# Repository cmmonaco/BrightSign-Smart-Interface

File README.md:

# BrightSign Smart Interface

The BrightSign Smart Interface (BSSI) is a system developed expand the capabilities of the [BrightSign](https://www.brightsign.biz/) digital signage controllers. A BrightSign has 8 GPIO pins used to control playback or out elements, however, the IO is limited to simple switching input making it less useful for interactive installations where complex input is used. The BSSI system is a set of boards that contain an Arduino along with support hardware specific to the interface type. This allows for the use of multiple and complex inputs and additional processing while controlling playback on the BrightSign. Current BrightSign players no longer support the connection type used in the BSSI.

## BSSI System

The BSSI system presently consists of three boards: the main board and two expansion boards: the GPIO board, and the industrial sensor board.

### Main Board

The main board contains the Arduino and serves as the primary interface to the BrightSign. The main board also contains a power adapter, allowing the Arduino and other peripherals to be powered externally rather than by the BrightSign.

### GPIO Board

The GPIO board simply break outs the remaining Arduino IO to headers. The board has locations on each pin for pull-up resistors and pins 10 and 11 are buffered (this can be bypassed).

### Industrial Sensor Board

The industrial sensor board can accept up to 7 channels of NPN type industrial sensors, 8 digital GPIO, and two analog inputs. It uses a port expander IC to achieve the high number of GPIO in addition to the sensor channels. The NPN sensor are connected using the following hardware interface:

## BSSI Library

An Arduino library for use the the BrightSign Smart Interface is also available. See README located in library directory for details.

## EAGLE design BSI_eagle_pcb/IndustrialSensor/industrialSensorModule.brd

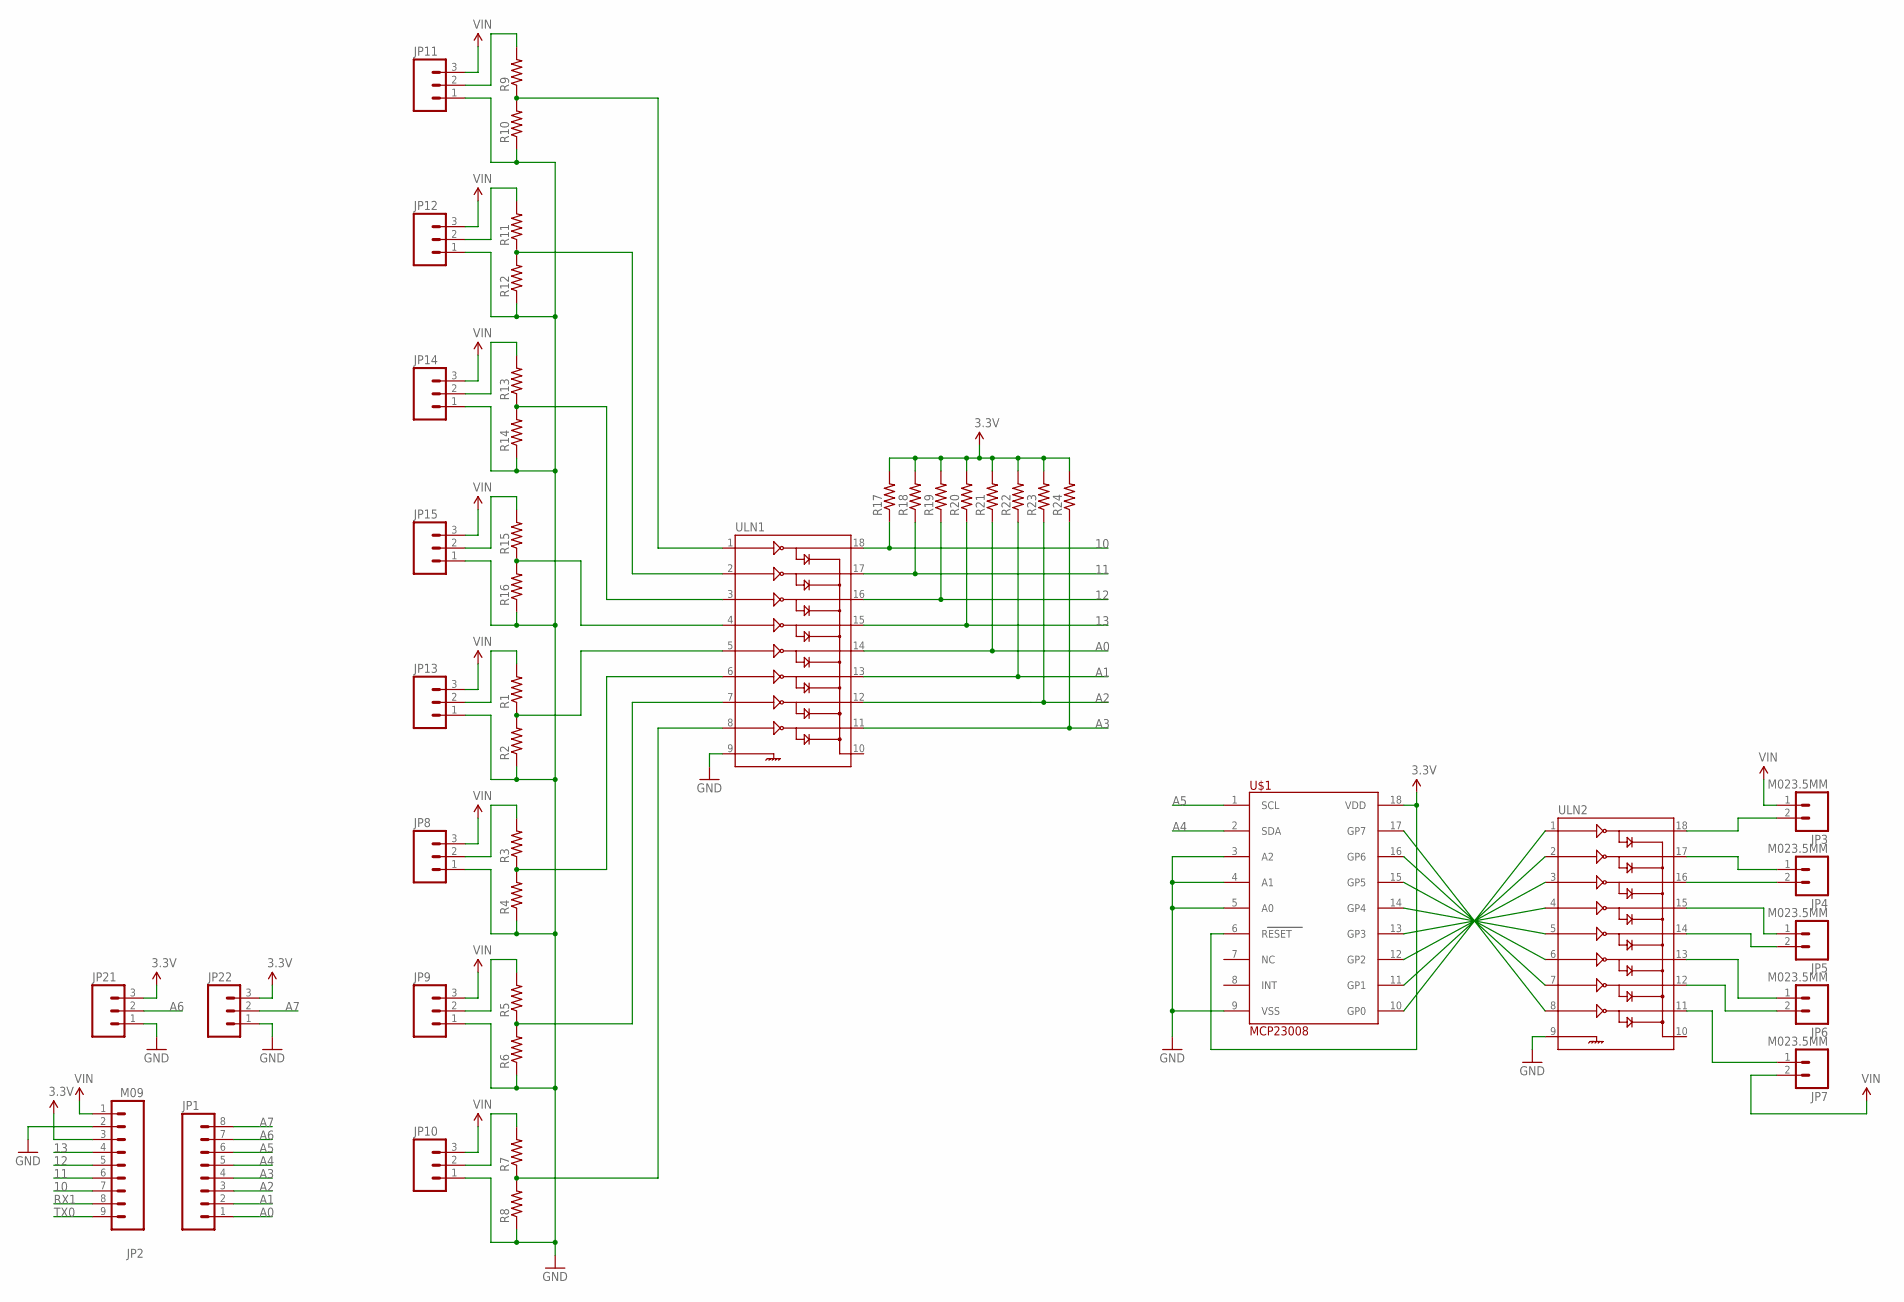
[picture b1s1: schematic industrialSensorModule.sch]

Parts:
JP1: M081X08; 1X08
JP2: M09; 1X09
JP3, JP4, JP5, JP6, JP7: M023.5MM; SCREWTERMINAL-3.5MM-2
JP8, JP9, JP10, JP11, JP12, JP13, JP14, JP15, JP21, JP22: M03SCREW; SCREWTERMINAL-3.5MM-3
R1, R2, R3, R4, R5, R6, R7, R8, R9, R10, R11, R12, R13, R14, R15, R16, R17, R18, R19, R20, R21, R22, R23, R24: RESISTOR1206; 1206
U$1: MCP23008; SOICW-18
ULN1, ULN2: ULN2803SOICW; SO18L

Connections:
3.3V: JP2.3, JP21.3, JP22.3, R17.2, R18.2, R19.2, R20.2, R21.2, R22.2, R23.2, R24.2, U$1.6 (RESET), U$1.18 (VDD)
10: JP2.7, R17.1, ULN1.18
11: JP2.6, R18.1, ULN1.17
12: JP2.5, R19.1, ULN1.16
13: JP2.4, R20.1, ULN1.15
A0: JP1.1, R21.1, ULN1.14
A1: JP1.2, R22.1, ULN1.13
A2: JP1.3, R23.1, ULN1.12
A3: JP1.4, R24.1, ULN1.11
A4: JP1.5, U$1.2 (SDA)
A5: JP1.6, U$1.1 (SCL)
A6: JP1.7, JP21.2
A7: JP1.8, JP22.2
GND: JP2.2, JP8.1, JP9.1, JP10.1, JP11.1, JP12.1, JP13.1, JP14.1, JP15.1, JP21.1, JP22.1, R2.1, R4.1, R6.1, R8.1, R10.1, R12.1, R14.1, R16.1, U$1.3 (A2), U$1.4 (A1), U$1.5 (A0), U$1.9 (VSS), ULN1.9, ULN2.9
unnamed: R1.1, R2.2, ULN1.5
unnamed: JP13.2, R1.2
unnamed: R3.1, R4.2, ULN1.6
unnamed: JP8.2, R3.2
unnamed: R5.1, R6.2, ULN1.7
unnamed: JP9.2, R5.2
unnamed: R7.1, R8.2, ULN1.8
unnamed: JP10.2, R7.2
unnamed: R9.1, R10.2, ULN1.1
unnamed: JP11.2, R9.2
unnamed: R11.1, R12.2, ULN1.2
unnamed: JP12.2, R11.2
unnamed: R13.1, R14.2, ULN1.3
unnamed: JP14.2, R13.2
unnamed: R15.1, R16.2, ULN1.4
unnamed: JP15.2, R15.2
unnamed: U$1.10 (GP0), ULN2.1
unnamed: U$1.11 (GP1), ULN2.2
unnamed: U$1.12 (GP2), ULN2.3
unnamed: U$1.13 (GP3), ULN2.4
unnamed: U$1.14 (GP4), ULN2.5
unnamed: U$1.15 (GP5), ULN2.6
unnamed: U$1.16 (GP6), ULN2.7
unnamed: U$1.17 (GP7), ULN2.8
unnamed: JP3.2, ULN2.18
unnamed: JP4.1, ULN2.17
unnamed: JP4.2, ULN2.16
unnamed: JP5.1, ULN2.15
unnamed: JP5.2, ULN2.14
unnamed: JP6.1, ULN2.13
unnamed: JP6.2, ULN2.12
unnamed: JP7.1, ULN2.11
RX1: JP2.8
TX0: JP2.9
VIN: JP2.1, JP3.1, JP7.2, JP8.3, JP9.3, JP10.3, JP11.3, JP12.3, JP13.3, JP14.3, JP15.3

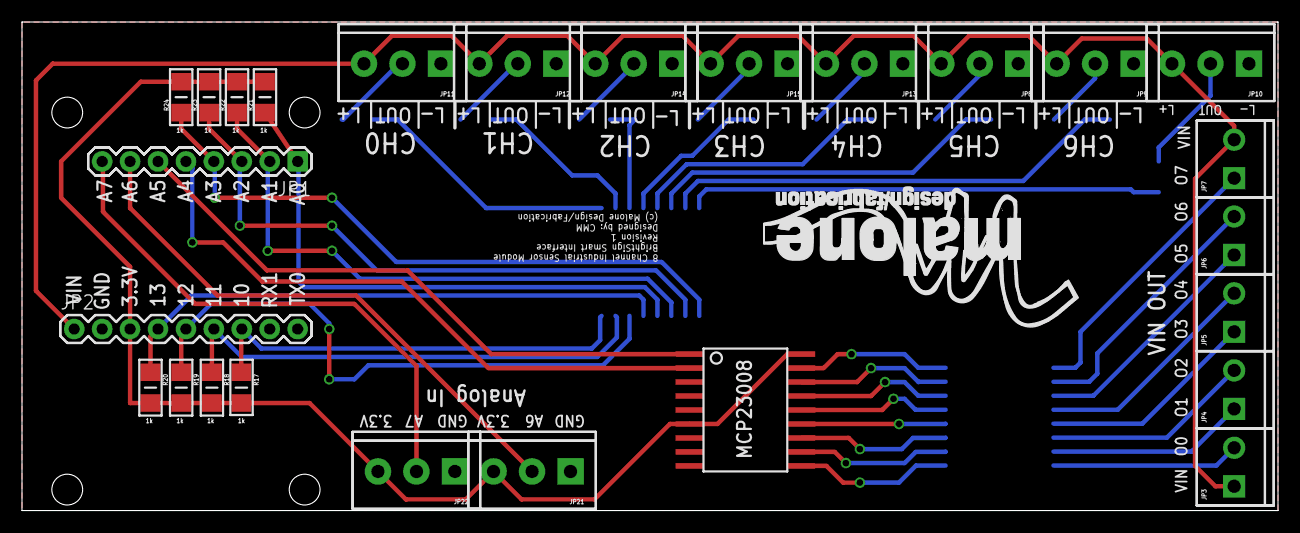
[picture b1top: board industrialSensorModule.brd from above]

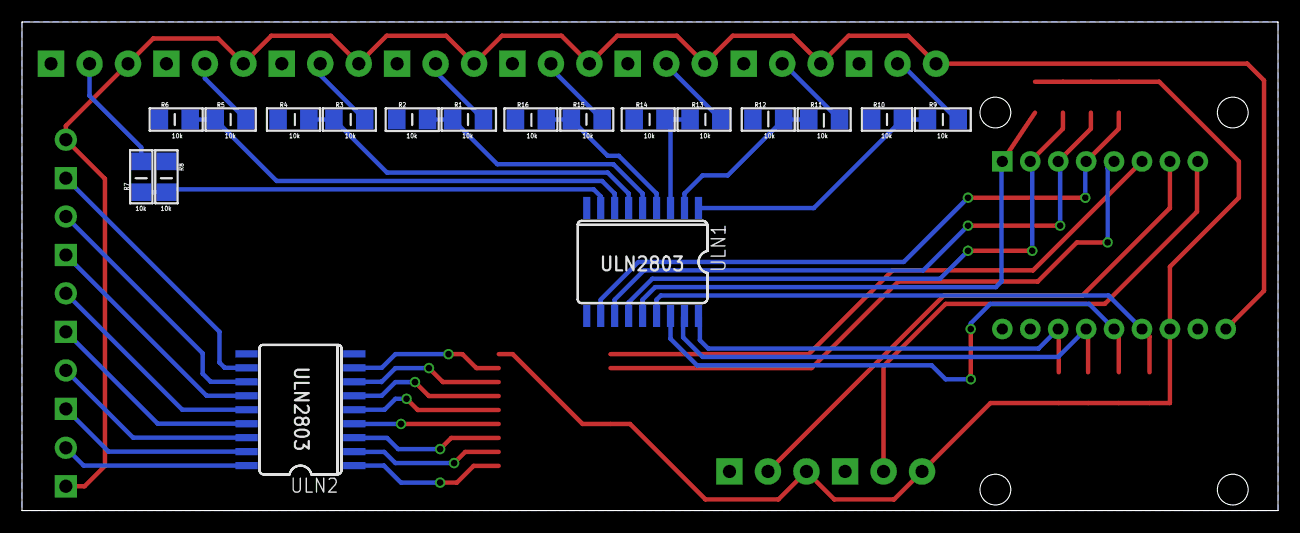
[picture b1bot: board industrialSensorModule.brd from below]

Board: 2 copper layers, 114.2 x 44.4 mm, 45 parts (18 on the bottom side), 47 nets.

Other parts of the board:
U$2: MALONE_LOGO

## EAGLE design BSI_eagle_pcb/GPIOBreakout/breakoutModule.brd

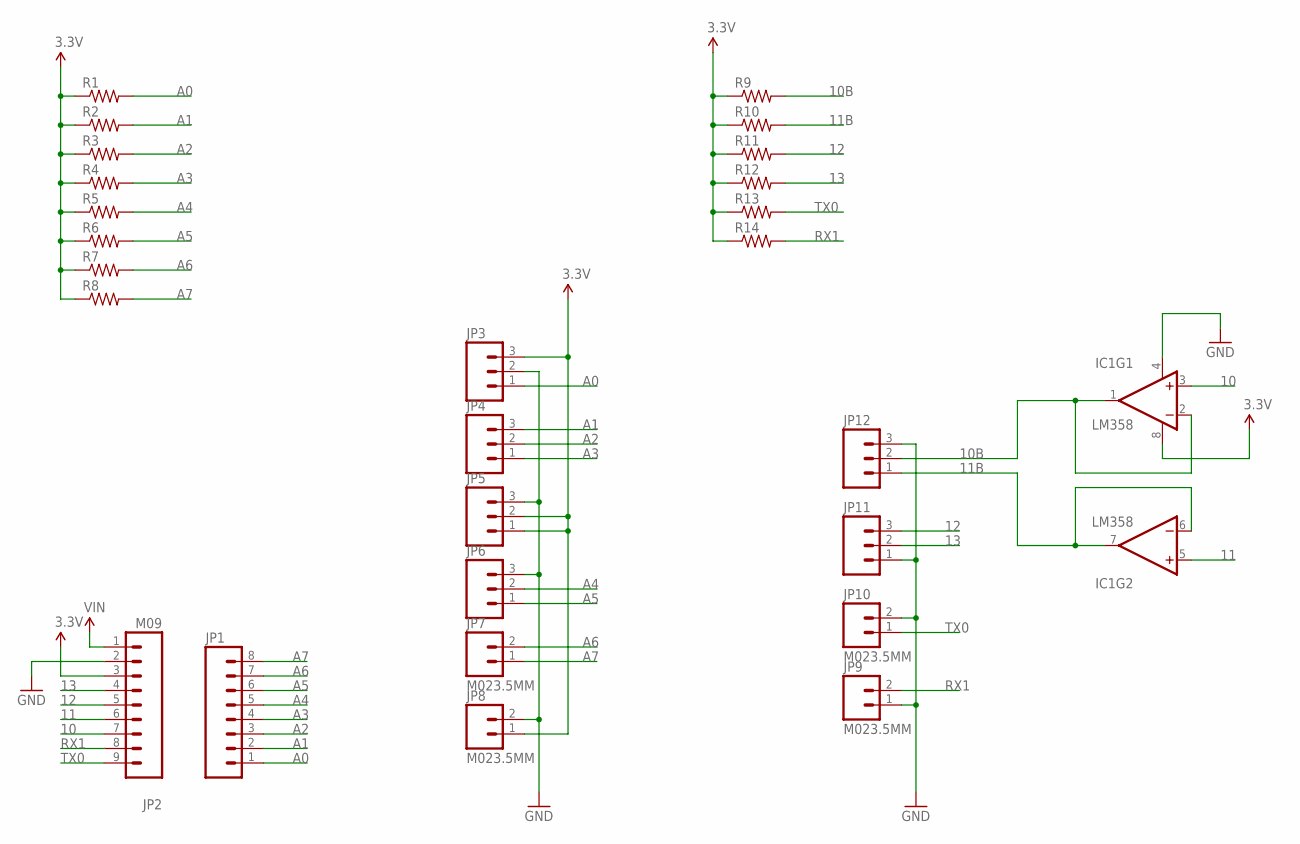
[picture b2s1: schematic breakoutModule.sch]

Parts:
IC1: LM358; DIP08
JP1: M081X08; 1X08
JP2: M09; 1X09
JP3, JP4, JP5, JP6, JP11, JP12: M03SCREW; SCREWTERMINAL-3.5MM-3
JP7, JP8, JP9, JP10: M023.5MM; SCREWTERMINAL-3.5MM-2
R1, R2, R3, R4, R5, R6, R7, R8, R9, R10, R11, R12, R13, R14: RESISTOR1206; 1206

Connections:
3.3V: IC1.8 (V+), JP2.3, JP3.3, JP5.1, JP5.2, JP8.1, R1.1, R2.1, R3.1, R4.1, R5.1, R6.1, R7.1, R8.1, R9.1, R10.1, R11.1, R12.1, R13.1, R14.1
10: IC1.3 (+IN), JP2.7
10B: IC1.1 (OUT), IC1.2 (-IN), JP12.2, R9.2
11: IC1.5 (+IN), JP2.6
11B: IC1.6 (-IN), IC1.7 (OUT), JP12.1, R10.2
12: JP2.5, JP11.3, R11.2
13: JP2.4, JP11.2, R12.2
A0: JP1.1, JP3.1, R1.2
A1: JP1.2, JP4.3, R2.2
A2: JP1.3, JP4.2, R3.2
A3: JP1.4, JP4.1, R4.2
A4: JP1.5, JP6.2, R5.2
A5: JP1.6, JP6.1, R6.2
A6: JP1.7, JP7.2, R7.2
A7: JP1.8, JP7.1, R8.2
GND: IC1.4 (V-), JP2.2, JP3.2, JP5.3, JP6.3, JP8.2, JP9.1, JP10.2, JP11.1, JP12.3
RX1: JP2.8, JP9.2, R14.2
TX0: JP2.9, JP10.1, R13.2
VIN: JP2.1

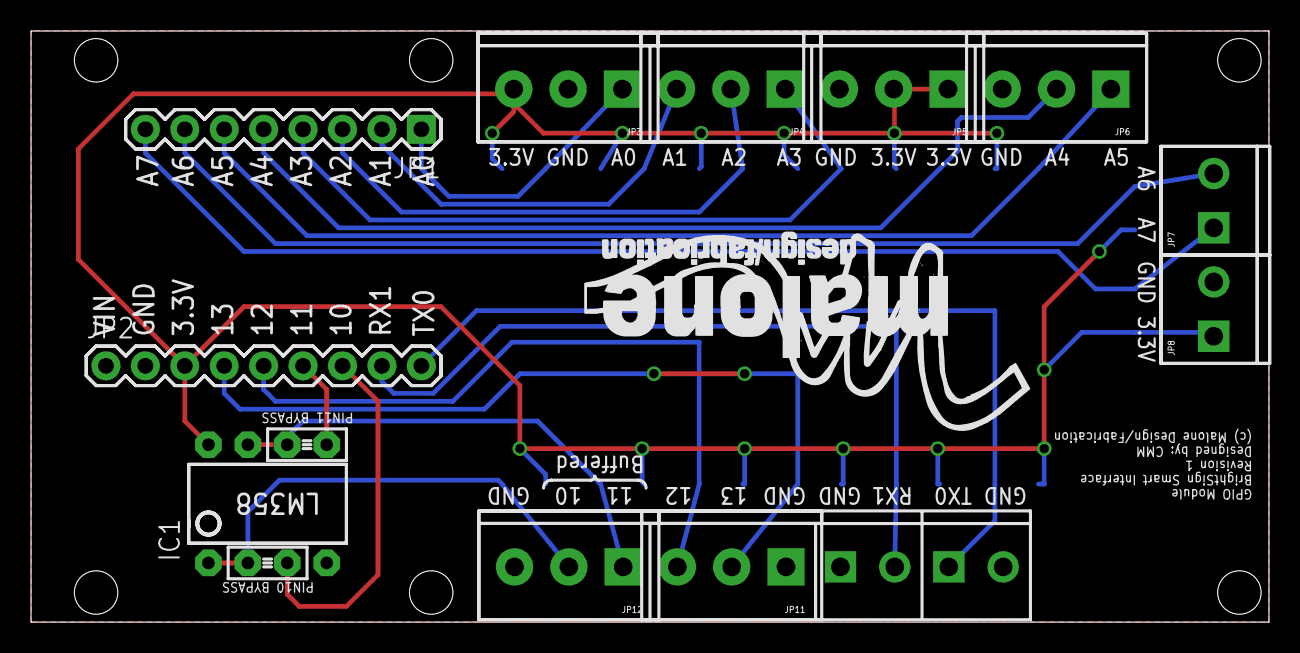
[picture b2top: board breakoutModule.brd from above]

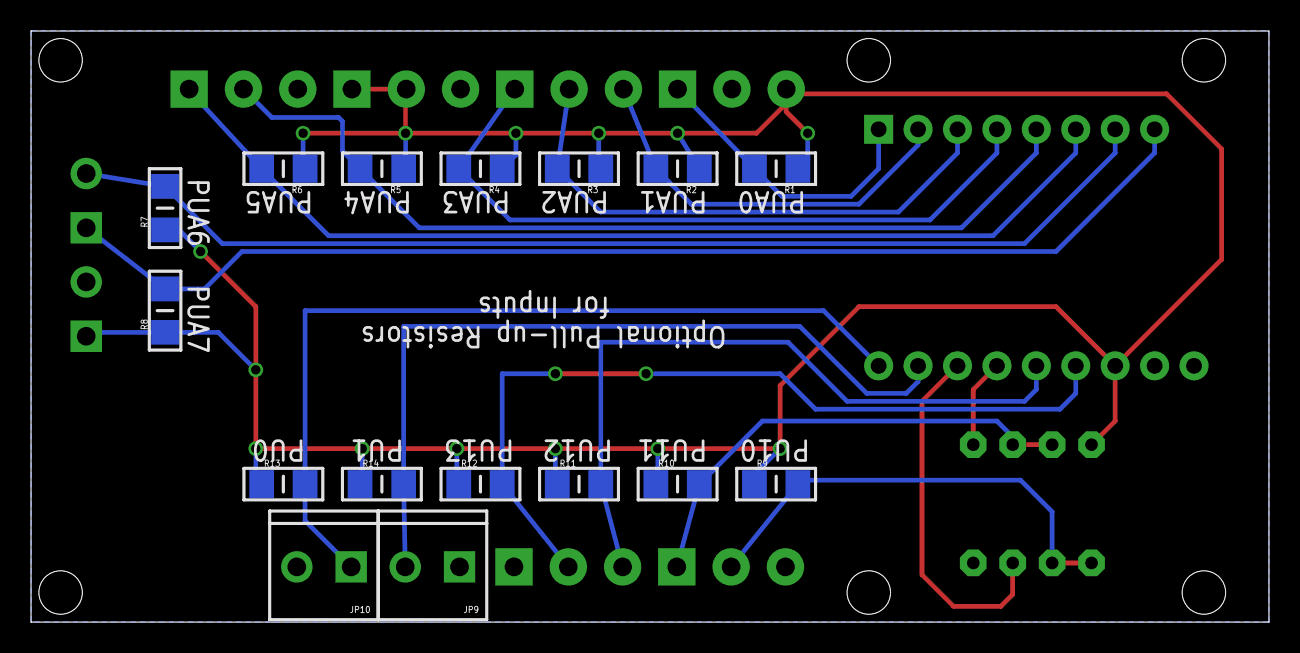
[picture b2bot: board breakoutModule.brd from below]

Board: 2 copper layers, 79.8 x 38.1 mm, 28 parts (16 on the bottom side), 18 nets.

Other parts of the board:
U$1: MALONE_LOGO

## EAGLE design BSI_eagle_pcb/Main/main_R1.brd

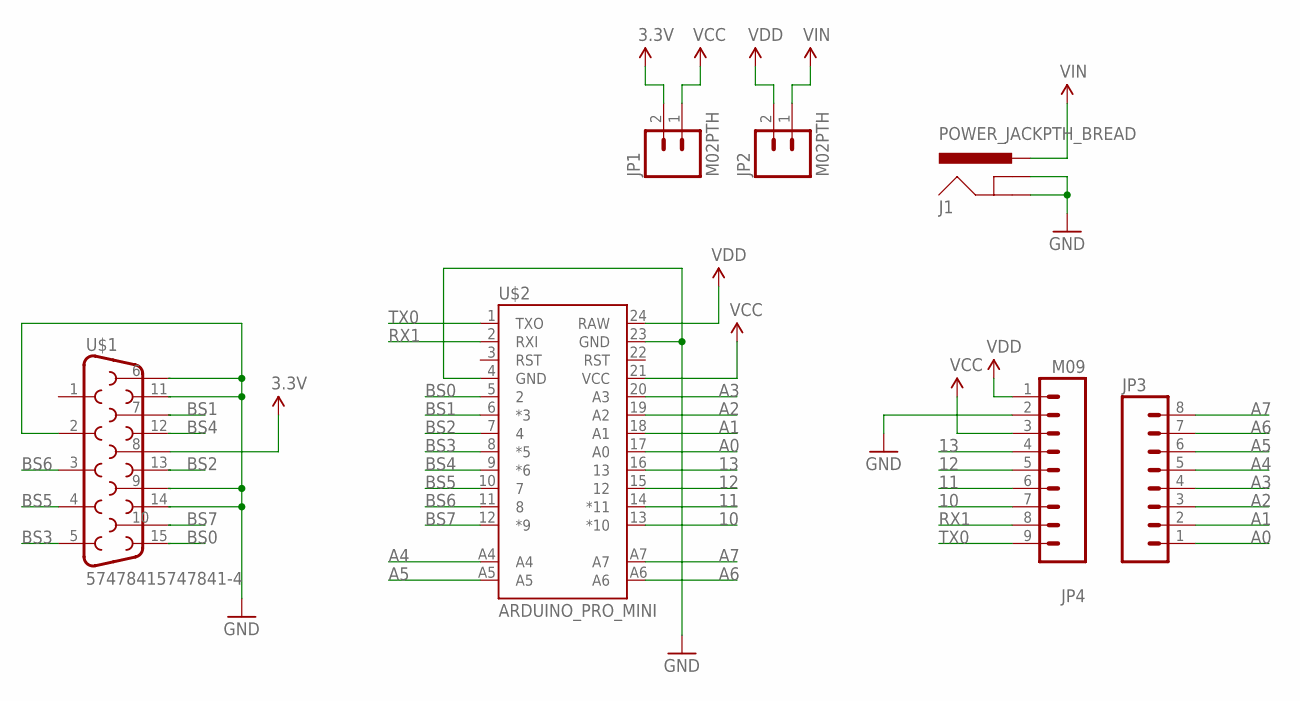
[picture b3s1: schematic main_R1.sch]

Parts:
J1: POWER_JACKPTH_BREAD; POWER_JACK_PTH_BREAD
JP1, JP2: M02PTH; 1X02
JP3: M081X08; 1X08
JP4: M09; 1X09
U$1: 57478415747841-4; 5747841
U$2: ARDUINO_PRO_MINI

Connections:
3.3V: JP1.2, U$1.8
10: JP4.7, U$2.13 (*10)
11: JP4.6, U$2.14 (*11)
12: JP4.5, U$2.15 (12)
13: JP4.4, U$2.16 (13)
A0: JP3.1, U$2.17 (A0)
A1: JP3.2, U$2.18 (A1)
A2: JP3.3, U$2.19 (A2)
A3: JP3.4, U$2.20 (A3)
A4: JP3.5, U$2.A4
A5: JP3.6, U$2.A5
A6: JP3.7, U$2.A6
A7: JP3.8, U$2.A7
BS0: U$1.15, U$2.5 (2)
BS1: U$1.7, U$2.6 (*3)
BS2: U$1.13, U$2.7 (4)
BS3: U$1.5, U$2.8 (*5)
BS4: U$1.12, U$2.9 (*6)
BS5: U$1.4, U$2.10 (7)
BS6: U$1.3, U$2.11 (8)
BS7: U$1.10, U$2.12 (*9)
GND: J1.GND, J1.GNDBREAK, JP4.2, U$1.2, U$1.6, U$1.9, U$1.11, U$1.14, U$2.4 (GND), U$2.23 (GND)
RX1: JP4.8, U$2.2 (RXI)
TX0: JP4.9, U$2.1 (TXO)
VCC: JP1.1, JP4.3, U$2.21 (VCC)
VDD: JP2.2, JP4.1, U$2.24 (RAW)
VIN: J1.PWR, JP2.1

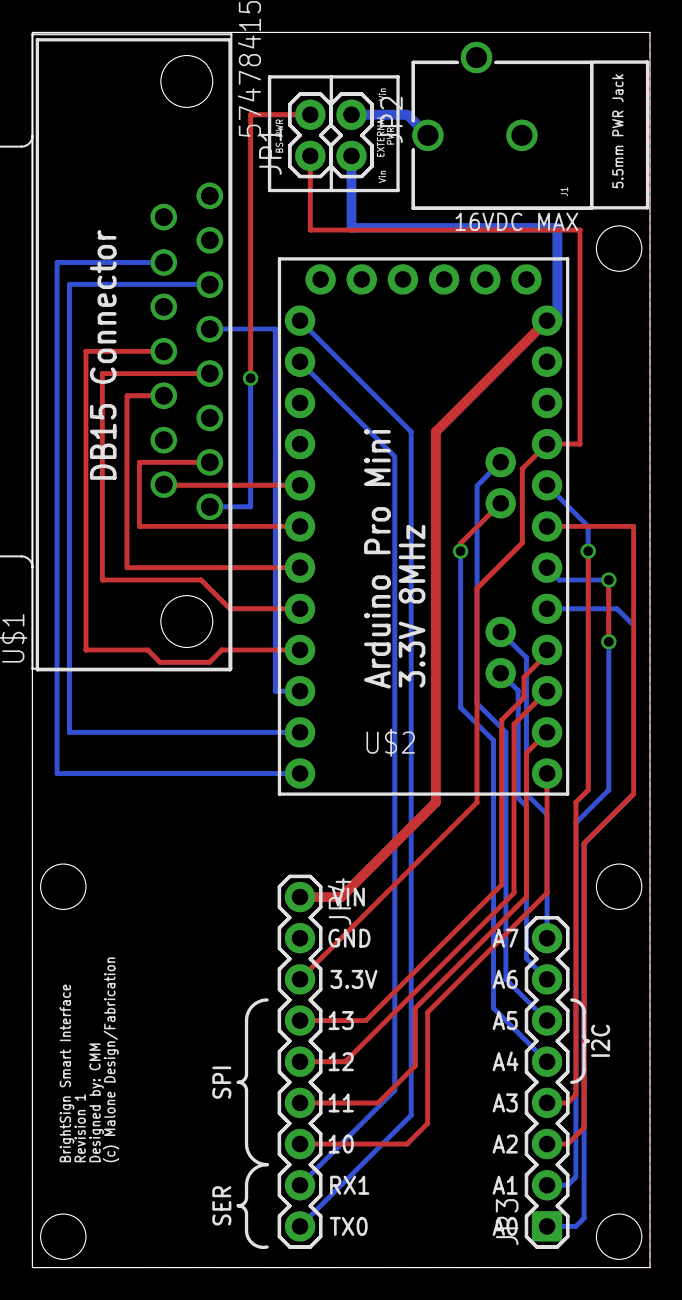
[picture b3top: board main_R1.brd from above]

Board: 2 copper layers, 38.1 x 76.2 mm, 7 parts (0 on the bottom side), 27 nets.

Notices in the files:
parts and their libraries:
SparkFun-Connectors: Licensing: Creative Commons ShareAlike 4.0 International - https://creativecommons.org/licenses/by-sa/4.0
